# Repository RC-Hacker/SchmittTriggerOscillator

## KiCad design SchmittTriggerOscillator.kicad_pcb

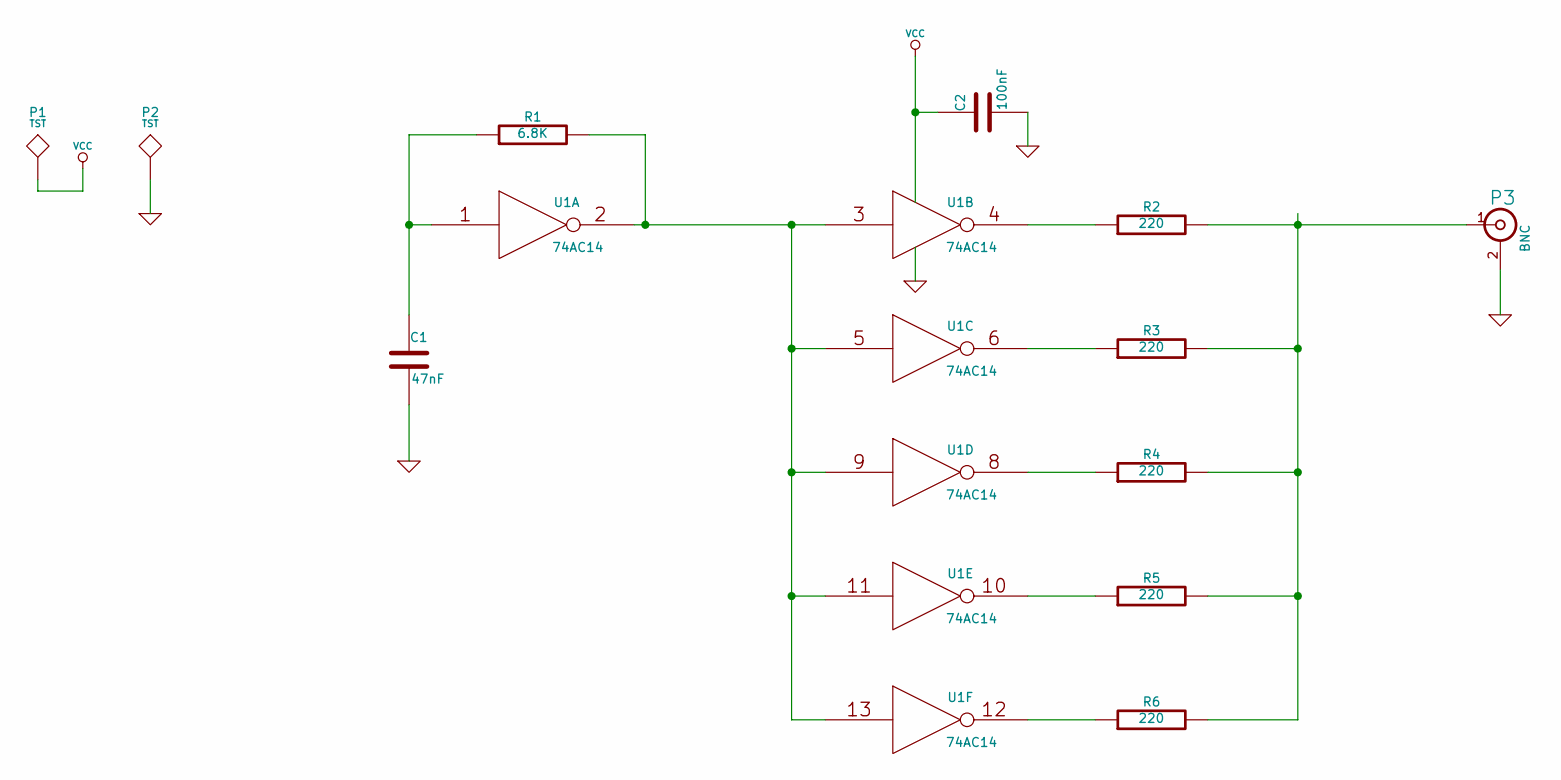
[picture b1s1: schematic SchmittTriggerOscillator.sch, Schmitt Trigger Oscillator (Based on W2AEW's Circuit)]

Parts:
C1: 47nF
C2: 100nF
P1, P2: TST
P3: BNC
R1: 6.8K
R2, R3, R4, R5, R6: 220
U1: 74AC14

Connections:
GND: C1.2, C2.2, P2.1, P3.2 (Ext), U1.7 (GND)
unnamed: C1.1, R1.1, U1.1
unnamed: P3.1 (In), R2.2, R3.2, R4.2, R5.2, R6.2
unnamed: R6.1, U1.12
unnamed: R5.1, U1.10
unnamed: R4.1, U1.8
unnamed: R3.1, U1.6
unnamed: R2.1, U1.4
unnamed: R1.2, U1.2, U1.3, U1.5, U1.9, U1.11, U1.13
VCC: C2.1, P1.1, U1.14 (VCC)

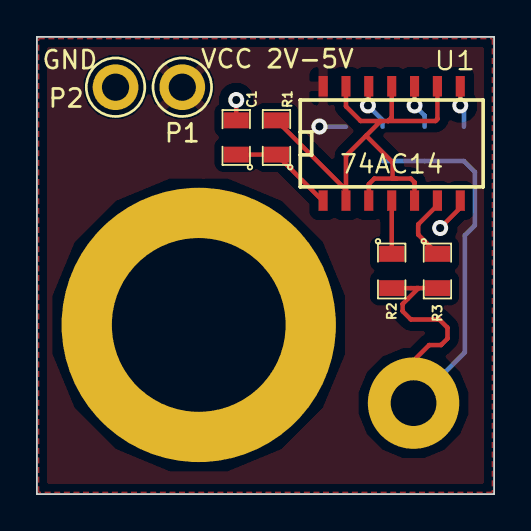
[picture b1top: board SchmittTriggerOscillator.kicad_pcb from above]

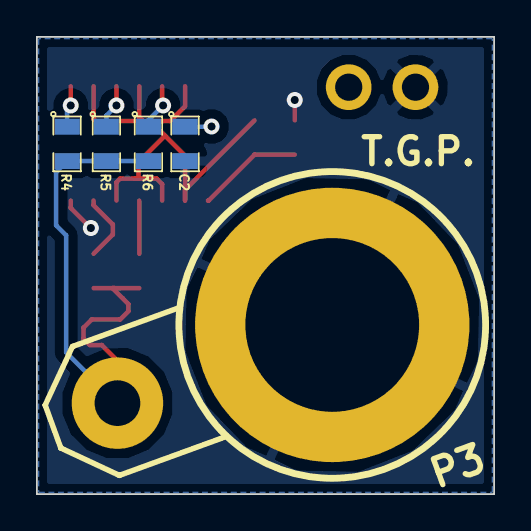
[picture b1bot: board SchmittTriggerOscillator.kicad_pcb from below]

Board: 2 copper layers, 25.4 x 25.4 mm, 12 parts (5 on the bottom side), 10 nets.
